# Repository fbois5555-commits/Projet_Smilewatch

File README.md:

# SmileWatch — Montre Connectée Hybride Haute Précision

> **Projet R&D — Conception mécatronique, électronique et horlogère avancée.**  
> Montre hybride alliant l'élégance et la sobriété d'un mouvement analogique à aiguilles, la discrétion d'un affichage numérique micro-OLED, et des capteurs biomédicaux de grade clinique, sans dépendre d'une application propriétaire grâce aux normes universelles Bluetooth SIG.

---

## 🌟 Vision & Philosophie du Projet

La **SmileWatch** est une montre hybride conçue pour répondre à un cahier des charges exigeant :
1. **Élégance horlogère & Discrétion** : Un vrai cadran horloger avec aiguilles physiques animées par un mouvement électromécanique, intégrant subtilement un écran micro-OLED 0.5" pour les notifications et les métriques de santé.
2. **Standard ouvert sans application smartphone dédiée** : Exploitation native des profils Bluetooth SIG standards (CTS, ANCS, HRS, HTS, BAS, DIS) permettant à la montre de fonctionner directement avec iOS et Android (synchronisation de l'heure, notifications directes du smartphone, suivi santé sur Apple Santé / Google Health Connect) sans application tierce requise.
3. **Précision biomédicale** : Capteur optique PPG (fréquence cardiaque & SpO2) et capteur de température cutanée à précision médicale (±0.1 °C) couplé à un insert thermique dédié.
4. **Zéro connecteur / Étanchéité totale** : Châssis métallique monobloc étanche avec recharge inductive sans fil Qi et programmation/test interne via Tag-Connect.

---

## ✨ Fonctionnalités Embarquées Complètes

- **Affichage & Énergie** : 9 écrans × 3 vues (27 vues), mode dynamique `split_6h`, pause mécanique des aiguilles Miyota devant la pilule OLED (`:24..:35`), luminosité adaptative (`VEML6030` → `CH1115`), allumage au regard (`Look-to-Wake`), Mode Nuit / DND, sommeil profond `STOP2`, coupure `+5V_HR` hors séance, charge sans fil Qi (`BQ24040`) et Mode Survie Extrême (`< 10 %` : Miyota seule, podomètre et capteurs coupés).
- **19 Sports, Triathlon & Coach IA** : Musculation, Course, Natation 25m, Vélo, HIIT/Tabata, Rando, Tennis, Boxe, Rameur, Yoga/Cohérence 5s/5s, Corde à sauter, Escalade, Marche rapide, Trail (hydratation 20m), Gainage 30s, Padel, Golf, Ski, Collectif + Triathlon multi-étapes. Détection auto zéro-clic (`LSM6DSOX MLC`), calibration piste `400m/1000m`, calibration GPS/pas BLE, Coach Zones FC (`Z1–Z5`), optimiseur de charge aiguë/chronique et `HRR60`.
- **Santé, Sommeil & Sécurité** : FC, SpO2, HRV (RMSSD), Body Battery, Stress, alerte tachycardie au repos (`>105 BPM` immobile 10 min), réveil doux (`-20 min`), Résumé Réveil + détection pré-maladie (`TMP117` + RHR + HRV), détection & programmation de sieste, détection de chute + compte à rebours SOS `10s` + contact `ICE`.
- **Quotidien, Mémoire & WebBLE Optionnel** : Lampe torche OLED, Chronomètre/Timer, Pomodoro (`25m/5m`), double fuseau horaire, notifications ANCS, GPS Turn-by-Turn, Météo/Agenda, contrôle média/photo BLE HID, alerte sédentarité optionnelle (`50 min`), diagnostic I2C1, FOTA BLE, buffer circulaire Flash `90 %` (`328/365` j) avec rappel et horodatage, plus compagnon WebBLE 0 € ([smilewatch_web.html](smilewatch_web.html)) avec export Strava `.TCX` / `.CSV`.

## 📚 Documentation par Dossier

- [Code/](Code/README.md) — Firmware STM32WB55, drivers I2C1/OLED/Miyota, moteur UI & Flash.
- [Kicad/](Kicad/README.md) — Schémas, PCB 6 couches, antenne RF & empilement.
- [3D/](3D/README.md) — Boîtier Acier 316L SLM/CNC, posage d'assemblage O4 & mécanique.
- [Fabrication_assemblage/](Fabrication_assemblage/README.md) — BOM, plans de montage, étanchéité & procédures.
- [Datasheet/](Datasheet/README.md) — Fiches techniques des composants critiques.

---

## 🛠️ Spécifications Techniques

| Domaine | Caractéristique | Spécification |
| :--- | :--- | :--- |
| **Boîtier / Carrure** | Matériau & Fabrication | **Acier Inox 316L** en **fabrication additive métallique (SLM / DMLS)** avec **reprises d'usinage CNC** des portées critiques (joints, portées d'étanchéité, lunette). |
| **Glace** | Supérieure & Inférieure | Glace supérieure en **Saphir plat** avec joint d'étanchéité Hytrel/Téflon ; fenêtre inférieure en verre minéral optique scellé à la colle UV pour le capteur PPG. |
| **Cadran** | Conception | **Cadran usiné en PCB (FR4 0.4 mm)** faisant office de cadran décoratif (sérigraphie/dorure, index, masquage) avec fenêtre découpée pour l'OLED et passage d'aiguilles. |
| **Mouvement analogique**| Horlogerie | Mouvement quartz **Miyota 2035 modifié (sans couronne)**, dont la bobine du moteur pas-à-pas est directement pilotée par le microcontrôleur via des impulsions électriques étalonnées. |
| **Afficheur numérique** | Écran | **PMOLED 0.5" monochrome (88 × 48 pixels)**, contrôleur **CH1115**, interface I2C, nappe 14 broches repliée sous le cadran avec écran acrylique de protection. |
| **Microcontrôleur (MCU)**| Processeur & Sans-fil | **STMicroelectronics STM32WB55** (Dual-Core : ARM Cortex-M4 @ 64 MHz pour l'applicatif + Cortex-M0+ dédié à la stack RF BLE 5.4), filtre RF intégré **MLPF-WB-02D3**, antenne céramique 2.4 GHz **Johanson 2450AT**. |
| **Capteurs** | Biomédical & Mouvement | • **TMP117** : Température corporelle haute précision (±0.1 °C de grade médical), interfacé via un pont/pad thermique métallique.<br>• **MAX30101** : Capteur optique PPG (Fréquence cardiaque & Oxymétrie de pouls SpO2) avec masque optique Kapton noir anti-diaphonie (120 µm).<br>• **LSM6DSOX** : IMU 6 axes (accéléromètre + gyroscope) avec Machine Learning Core (MLC) pour le podomètre et la reconnaissance de gestes au poignet ultra-basse consommation.<br>• **VEML6030** : Capteur de luminosité ambiante avec guide d'onde lumineux pour l'ajustement automatique de l'OLED. |
| **Interface & Haptique**| I/O & Retours | Contrôleur haptique évolué **TI DRV2605L** + vibreur CMS **HD-EMB1204-SM** ; 2 boutons poussoirs tactiles latéraux étanches **Alps Alpine SKSLLAE010**. |
| **Batterie & Autonomie**| Alimentation | Pile bouton rechargeable Li-Ion **LIR3048 (280 mAh, 3.7 V)** maintenue par contact latéral CMS Harwin (S1921-46R) et calage en mousse Poron. |
| **Recharge** | Sans fil | Récepteur sans fil Qi **TI BQ51003** + bobine de réception Würth Elektronik (**760308101309**) + chargeur linéaire Li-Ion **TI BQ24040**. |
| **Conversion d'énergie**| PMIC & Régulation | Convertisseur élévateur **TPS61023DRLR** (+5.0V pour LEDs capteurs, `R23/R24 = 150k/20k`, inductance **1.0 µH** `DFE18SBN1R0ME0L` `0603`), LDOs +3.3V / +1.8V **TPS7A0233DBVR / TPS7A0218PDBVR** (25 nA), protection batterie **AP9101CAK-ATTRG1** (`C5588142`). |
| **Débogage & Flash** | Connectique | Empreinte **Tag-Connect TC2030-IDC-NL** (SWD 6 broches sans embase physique). |

---

## 📡 Stratégie Bluetooth : Profils Standards & Écosystème

Pour garantir une pérennité totale, une compatibilité multi-OS immédiate et s'affranchir du développement/maintenance d'une application mobile tierce, la SmileWatch implémente directement les **spécifications et profils standardisés Bluetooth SIG et Apple/Android** :

* **CTS (Current Time Service - `0x1805`)** : Synchronisation automatique et transparente de l'heure et du fuseau horaire dès la connexion au smartphone.
* **ANCS (Apple Notification Center Service)** & **Notification Provider Android** : Réception native des alertes (appels entrants, SMS, calendrier, messageries) directement relayées sur l'écran OLED sans passer par une app intermédiaire.
* **HRS (Heart Rate Service - `0x180D`)** : Transmission standardisée de la fréquence cardiaque, reconnue nativement par Apple Santé, Google Health Connect, Strava, Garmin, etc.
* **HTS (Health Thermometer Service - `0x1809`)** : Exportation de la température corporelle clinique mesurée par le TMP117.
* **BAS (Battery Service - `0x180F`)** : Niveau de batterie affiché nativement dans le widget batterie du smartphone.
* **DIS (Device Information Service - `0x180A`)** : Renseignement du nom de modèle, révision hardware, firmware et numéro de série.

---

## 🧩 Architecture Matérielle & Modulaire (Notice V3.8)

L'assemblage physique de la montre repose sur une **architecture recto-verso modulaire à deux sous-ensembles**, assemblés selon une séquence millimétrée :

### 1. Module Supérieur (Face avant)
* **Outillage impératif** : Utilisation d'une **cale 3D d'assemblage (posage O4)** insérée par le bas de la carrure pour encaisser l'effort axial lors du chassage de la glace saphir et préserver le mouvement Miyota.
* **Mouvement horloger** : Positionnement du Miyota 2035 au centre, coiffé par le PCB supérieur (chevauchement de 0.8 mm). Soudure des micro-fils de la bobine du Miyota directement sur les pastilles de 1 mm du PCB supérieur.
* **Carrure flottante & Écran** : Architecture à carrure 316L électriquement flottante (suppression de l'époxy conductrice à l'argent initialement prévue en V3.8, le plan de masse interne 6 couches assurant le contrepoids RF). Soudure directe à plat de la nappe 14 broches (pas 0.62 mm) de l'OLED CH1115, repliement et collage sous le cadran avec fenêtre acrylique.
* **Aiguilles & Chassage Saphir** : Pose des aiguilles des heures et minutes à midi pile, pose du joint Téflon/Hytrel et chassage en force de la glace saphir à la presse d'établi. Retrait de la cale 3D par le bas.

### 2. Module Inférieur (Face arrière & Capteurs)
* **Module thermique** : Insert métallique chassé dans la base polymère, contact thermique avec le capteur TMP117 via pad élastomère.
* **Bobine Qi & Batterie** : Bobine Würth 760308101309 collée dans la base polymère + disque isolant Kapton. Insertion de la batterie LIR3048 (280 mAh) dans le contact latéral CMS, calée par pastille Poron.
* **Optique PPG** : Masque Kapton noir (120 µm) centré sur le MAX30101 (isolation optique émetteur/récepteur), scellement de la glace minérale inférieure à la colle UV.

### 3. Liaison Inter-Modules & Fermeture (Point de non-retour)
* **Interconnexion** : Connecteur THT (Samtec) assurant la liaison électrique rigide entre le PCB supérieur et le PCB capteur inférieur. Soudure par le dessous et arasage des broches à ras. Soudure des micro-fils de la bobine Qi.
* **Fermeture** : Graissage léger du joint torique périphérique (O-ring) de la base polymère et chassage en force du fond dans la carrure (compression axiale finale assurée par les mousses Poron).

---

## 📁 Arborescence du Projet

```text
Projet_Smilewatch/
├── 3D/                          # Fichiers CAO SolidWorks (Pièces .SLDPRT, Assemblages .SLDASM, STEP)
│   ├── carrure.SLDPRT/.STEP     # Boîtier principal (conçu pour impression 3D métal SLM + usinage)
│   ├── Cadran.SLDPRT            # Cadran horloger (conçu sur base PCB FR4 0.4mm)
│   ├── Carte_Capteur_V1/V2.step # Encombrement 3D de la carte capteurs
│   ├── Carte_V1 / Carte_V2.step # Encombrement 3D de la carte mère
│   ├── Miyato_2035.SLDPRT       # Modèle 3D du mouvement horloger
│   ├── Pad_thermique / Pont...  # Pièces de transfert thermique pour le TMP117
│   └── Montre.mp4               # Animation de rendu et cinématique d'assemblage
├── Code/                        # Firmware embarqué sous STM32CubeIDE
│   └── SmileWatch1/             # Projet STM32CubeMX / CubeIDE pour STM32WB55
│       ├── Core/                # Code source C applicatif (main.c, interruptions, init I2C/GPIO)
│       └── Drivers/             # HAL STM32WBxx et CMSIS
├── Commande/                    # Devis, références et paniers de composants (Mouser/Digikey/JLCPCB)
├── Datasheet/                   # Fiches techniques des composants électroniques
│   ├── V1/                      # Datasheets de l'architecture V1 (STM32WB5MMG SiP)
│   └── V2/                      # Datasheets de l'architecture V2 (STM32WB55, filtres, antenne)
├── Fabrication_assemblage/      # Guides et documents de fabrication
│   └── Notice_montage_montre.pdf# Manuel d'intégration mécanique modulaire recto-verso (V3.8)
├── Kicad/                       # Projets de CAO électronique KiCad
│   ├── Carte_V1/                # Première itération matérielle
│   ├── Carte_V2/                # Schémas hiérarchiques et PCB v2 (MCU, Alim Qi, Capteurs, Écran, Moteur)
│   │   ├── Carte_Capteur_V2/    # Sous-carte capteurs (TMP117, MAX30101, boost TPS61023, TCA9517D) & production/
│   │   └── production/          # Fichiers de fabrication PCB (Gerbers, Drill, CPL, BOM JLCPCB)
│   └── Composant/               # Empreintes et symboles personnalisés
├── Media/                       # Rendu 3D, photos, vues éclatées et transparentes
├── README.md                    # Présentation et documentation centrale du projet
└── REFLEXIONS.md                # Carnet d\'idées, backlog et points d\'attention techniques
```

---

## 🎯 Statut Actuel & Feuille de Route

- [x] **Architecture système & Sélection des composants** : Définition complète (STM32WB55 WLCSP-100, LIR3048 280 mAh, Qi BQ51003, capteurs cliniques).
- [x] **CAO Mécanique 3D (SolidWorks 2026) & PCB Cadran FR4** : Modélisation carrure, base, verres, posage O4 et conception du cadran horloger FR4 0.4 mm (dorure ENIG sur masque noir mat).
- [x] **Notice de montage modulaire** : Rédaction du manuel d'intégration mécanique (V3.8, mise à jour V3.9 prévue).
- [x] **Audit d'Ingénierie Global 360° (08 Novembre 2026)** : Inspection intégrale sans approximation des 3 PCB KiCad 10, des datasheets constructeurs et des 50 interférences SolidWorks de `Montre.SLDASM` (détails et correctifs consignés dans `REFLEXIONS.md` §13 et `suivi_projet.html`).
- [x] **Passe Corrective Électronique, Datasheets & BOM V2.1 (11 Novembre 2026)** :
  - **`Carte_V2`** : Polarité batterie `LIR3048` corrigée (`BT1` = `C22` latéral `+3V8`, `TP8` `6×6 mm` sur `GNDPWR`, `TP2` supprimé — *point d'attention : contact central plat excentré à $r=11.05\text{ mm}$ sans ressort*) ; switch OLED `Q1`/`Q2` câblé (`Q2.2` à `GND`, `Q1.2`+`R15` sur `+3V8`, `R13 = 560 kΩ`) ; RF corrigée (`R21`/`R24 = DNP` + `in_pos_files no`, Keepout 6 couches `ANT1`, quartz `Y1 = ABM13W 8 pF` + `12 pF C0G`) ; pont ADC `VBAT` (`2×1 MΩ + 100 nF` sur `PC4`), LDOs `TPS7A0233/18`, `R5 = 1.5 kΩ`, `R7 = DNP`, `C46 = 100 nF`, `R16 = 330 Ω`, `U4 = AP9101CAK-ATTRG1` (`C5588142`, Auto-Wake-Up), `C0G2_50V1 = 220 nF` (`C21120`), `R27 = 10 kΩ` (`C25744`, remplace `TH2`), `TH1 = 10k NTC` (`C91636`), assainissement complet des `JLCPCB Part#` passifs. **ERC = 0 erreur (62 warnings), DRC (règles projet) + parité = 0 violation, 0 non connecté** *(20 alertes `--severity-all` préexistantes connues sur `S1/S2` bord `0.17–0.19 mm` et freins thermiques `IC2`)*.
  - **`Carte_Capteur_V1` & `Cadran`** : Boost `+5.0V` migré vers **`TPS61023DRLR`** (`IC3`, `C919459`, stk `6 681`) + **`L1 = 1.0 µH` `0603` (`DFE18SBN1R0ME0L`, `C882989`, stk `2 188`)** + **`R23 = 150 kΩ` (`C25755`) / `R24 = 20 kΩ` (`C25765`)** + `C18/C19 = 10 µF` (`C96446`) ; **`U3 = TCA9517DR`** (`C182421`, **stk `5 738` en stock JLC**) inversé et rerouté Side A (`+1V8` MAX30101) / Side B (`+3V3` MCU) ; îlot thermique `B.Cu` + 2 vias + keepout `U2_Thermal_Iso` sous `TMP117` (`U2`). **ERC = 0 erreur (`11` warnings), DRC + parité = 0 violation** (`Cadran` inchangé avec marge OLED conservée : ERC `0` / DRC `0` erreur, `55` warnings sérigraphie bord).
  - **Datasheets & Livrables usine mis à jour** : `Datasheet/V2/` actualisé (`tps61023.pdf`, `tps7a02.pdf` EN `SBVS277C`, `ABM13W`, `NCP15XH103F0SRC`, `DFE18SBN1R0ME0L`, `Samtec_TW_Series`, `CL10A106MA8NRNC.pdf`, `GRM1555C1H222GA01D.pdf` ; retrait `MAX17220`, `AP2127`, `Hirose`, `74438323100`), packages **`production/`** (Gerbers `.zip`, Drill, IPC-356, `bom.csv`, `positions.csv`) régénérés pour les 3 cartes, BOM schémas `Carte_V2.csv` / `Carte_Capteur_V1.csv` à jour, et modèles **`3D/Carte_V2.3f.step`** / **`3D/Carte_Capteur_V2f.step`** ré-exportés.
- [x] **Finalisation Routage, Empreintes JLC & Modèles 3D `Carte_V2` (14 Novembre 2026)** :
  - **Empreintes & Modèles 3D** : Bibliothèque `Smilewatch_V2_JLC.pretty` et `Carte_V2.kicad_pcb` mises à jour avec chemins `.step` corrigés (`${KIPRJMOD}/../Composant/...`) pour `ANT1`, `FL1`, `Y1`, `Q3`, `IC2`, et création de `LD-SM-430.step` (`4,0 × 11,0 × 3,6 mm`) pour le moteur `M1`.
  - **Antenne `ANT1` & RF `50 Ω`** : Zone keep-out `4,0 × 6,0 mm` 6 couches intégrée à `ANT1` (`Pin 4 = FEED`, `Pin 1–3 = GND`), placée à `2,81 mm` du bord (`R = 19,45 mm`, un seul coin déborde de `0,35 mm`, `BT1` hors zone active) ; ligne coplanaire `GCPW` ajustée à **`0,135 mm`** / jeu **`0,10 mm`** pour le stackup **`JLC06081H-2116`** (`0,8 mm`, 6 couches, `0,1349 mm` sur l'`Impedance calculator` JLCPCB, ~100 € moins cher que `2313`), sur `U2.K4 → FL1 → Pi-network R21/R22/R24 → ANT1.4` avec plan `In1.Cu` continu et vias de couture `GND`.
  - **Prochaine étape immédiate (`19 Nov 2026` — Jalon critique `< 16 Déc`)** : **Carrures SLM 316L (`x4`, `3D/carrure_fabrication.SLDPRT`) payées et en attente de livraison** ; **taraud + 2× Miyota 2035 reçus (`18 Nov`)** ; **inversion des clips faite** et **firmware en très bonne voie**. Côté électronique : **`positions.csv` corrigé (`ANT1` `90°`, `IC1` `0°`, `IC4`/`IC6` `180°`, `IC8` `270°`)** ; à la réception de `U2` (**26 Nov**), ré-uploader `positions.csv`, vérifier `U4` (`bottom`) en 3D et lancer immédiatement le PCBA (`JLC06081H-2116`, `Depanel = Yes`, livraison express pour réception **avant le 16 décembre** — sinon reprise repoussée au **8 janvier** pour une fin le **22 janvier**).
- [ ] **Verrouillage avant commande Usine (Points Méca, Datasheets & Sourcing en attente)** :
  - **Mécanique CAO (`Montre.SLDASM`)** : Portée saphir (`+1.35 mm`), gorge O-ring ISO 3601 (25 %), `Batterie.SLDPRT` (`4.90 mm`) et `Canal_lum.SLDPRT` travaillés (`09/11`, proto PLA lancé) ; **inversion des clips `Base`/`carrure` effectuée** (`19 Nov`) ; `3D/carrure.SLDPRT` (`51,04 × 44,21 × 9,65 mm`) conservée aux cotes finales et **clone fabrication `3D/carrure_fabrication.SLDPRT` commandé en `x4` SLM 316L (`19 Nov`, payé — en attente livraison)** ; reprise prévue à réception : alésage tour + perçage + **chanfrein 45°** + taraudage poussoirs. **Contrôles restants sur `Base.SLDPRT` / assemblage** : statuer sur les composants `F.Cu` sous la dalle OLED (`Q1`, `Q2`, `7×0603` `[P0-MECA-7]`), confirmer poche sous `J1` + lamage Qi dans `Base.SLDPRT` `[P0-MECA-6]`, intégrer poussoirs étanches `Bouton.SLDASM` `[P1-MECA-9]` et vérifier dégagement radial `TPS61023`/`L1 0603` `[P1-MECA-10]`.
  - **Points d'attention Datasheets JLC (`V2.1`)** : **`U4` (`AP9101CAK-ATTRG1` `C5588142`, stk `162` ✅)** = variante `CAK` **Auto-Wake-Up** (`VCU=4.400 V` protégée en aval par `BQ24040` à `4.20 V`, `VDL=2.800 V` adaptée à la `LIR3048`, `0 V` autorisée) ; **`C0G2_50V1` (`C21120` `CL10B224KA8NNNC`)** = `220 nF 25 V X7R` (au lieu de `C0G 50 V`) sur résonance série Qi `10 µH` (`760308101309`) ; **`TPS61023` (`IC3`)** alimenté par `IC6` (`TPS7A0233` `200 mA` max ➔ pulses `MAX30101` `≤ 50 mA`), `+5.06 V` typ (`C19/C26 = 2×10 µF 25V X5R`).
  - **Sourcing JLCPCB SMT (`19 Nov 2026`)** : Tous les composants JLC de `Carte_Capteur_V1` sont en stock (`J1` main). Sur **`Carte_V2`** (`bom.csv` réaligné sur KiCad, `46` lignes / `99` composants) : **`IC1`, `IC8`, `FL1`, `TH1` sécurisés dans `My Parts`** ; `ANT1` (`646`), `Y1` (`380`), `M1` (`2 382`), `Q3` (`170 444`) en stock public ; **seul `U2` (`C1850399`) reste en attente de livraison (reporté au 26 Nov)** (activer **Epoxy Filled & Capped** + `JLC06081H-2116`). Hors-PCBA à souder/monter manuellement : `C39`, `J2`, `BT1`/`TP8`, `TP1`/`TP3`, `TP6`/`TP7`.
  - **Firmware `[P2-FW-16]`** : **En très bonne voie** (`19 Nov`).
- [ ] **Fabrication des prototypes matériels** :
  - Commande de la carrure en fabrication additive métallique (SLM/DMLS Inox 316L) + reprise CNC et fabrication de la Base.
  - Fabrication et assemblage PCB (PCBA JLCPCB pour carte mère 6 couches, carte capteurs et cadran).
- [ ] **Développement Firmware (`STM32WB55VGYx` WLCSP-100)** :
  - Création du nouveau projet STM32CubeIDE sur cible `STM32WB55VGYx` (remplaçant le squelette V1 `STM32WB5MMGHx`) avec `HSE 32 MHz`, `LSE` et pile BLE double-cœur (`STM32_WPAN` + OTA).
  - Implémentation des profils BLE standards (CTS, ANCS, HRS, HTS, BAS, DIS).
  - Pilote pas-à-pas bipolaire amorti (impulsion calibrée + freinage électrodynamique `LOW-LOW`) pour le mouvement Miyota 2035.
  - Driver I2C DMA pour l'affichage CH1115 (OLED 88×48) et les capteurs, et gestion veille ultra-basse consommation (`STOP 2` + réveil MLC `LSM6DSOX`).

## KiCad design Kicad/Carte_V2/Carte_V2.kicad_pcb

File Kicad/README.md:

# Kicad — Conception Électronique & PCB

Ce dossier regroupe les schémas électriques, le routage PCB et les bibliothèques KiCad de la SmileWatch.

## Points Clés Matériels

- **Architecture 6 couches** : séparation stricte des plans de masse analogique/RF/puissance et intégration dans un encombrement circulaire horloger.
- **Cœur RF & MCU** : `STM32WB55VGYx` (WLCSP-100), filtre RF intégré `MLPF-WB-02D3`, antenne céramique 2.4 GHz `Johanson 2450AT` avec carrure acier 316L flottante.
- **Capteurs I2C1** : `LSM6DSOX` (`0x6A`), `MAX30101` (`0x57`), `TMP117` (`0x48`), `VEML6030` (`0x10`), `DRV2605L` (`0x5A`), écran PMOLED `CH1115` (`0x3C`).
- **Alimentation & Recharge Qi** : Récepteur sans fil `BQ51003` + chargeur Li-Ion `BQ24040` pour pile `LIR3048`, boost `+5V` `TPS61023` commandé par `HR_5V_EN`, LDOs `TPS7A0233` / `TPS7A0218` (`25 nA`).
- **Programmation** : Empreinte `Tag-Connect TC2030-IDC-NL` (SWD 6 broches sans connecteur).

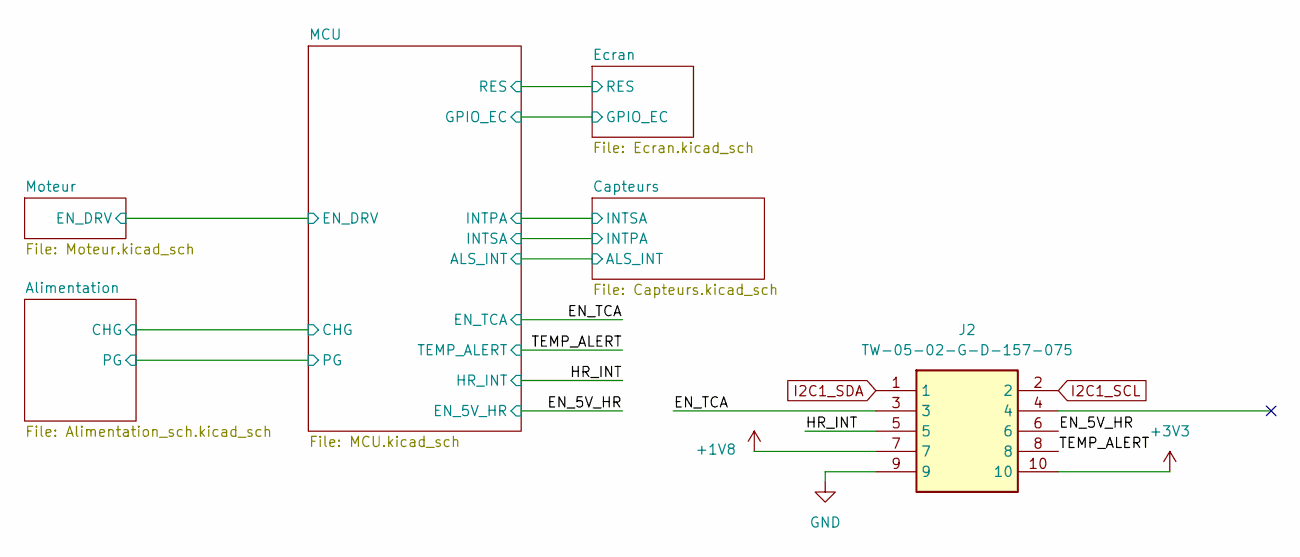
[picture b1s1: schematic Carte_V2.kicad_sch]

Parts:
J2: TW-05-02-G-D-157-075; HDRV10W51P200_2X5_1000X400X769P; Mouser Part Number 200-TW0502GD157075

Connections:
+1V8: J2.7; also elsewhere on the board
/EN_5V_HR: J2.6; also elsewhere on the board
/EN_TCA: J2.3; also elsewhere on the board
/HR_INT: J2.5; also elsewhere on the board
/TEMP_ALERT: J2.8; also elsewhere on the board
I2C1_SCL: J2.2; also elsewhere on the board
I2C1_SDA: J2.1; also elsewhere on the board

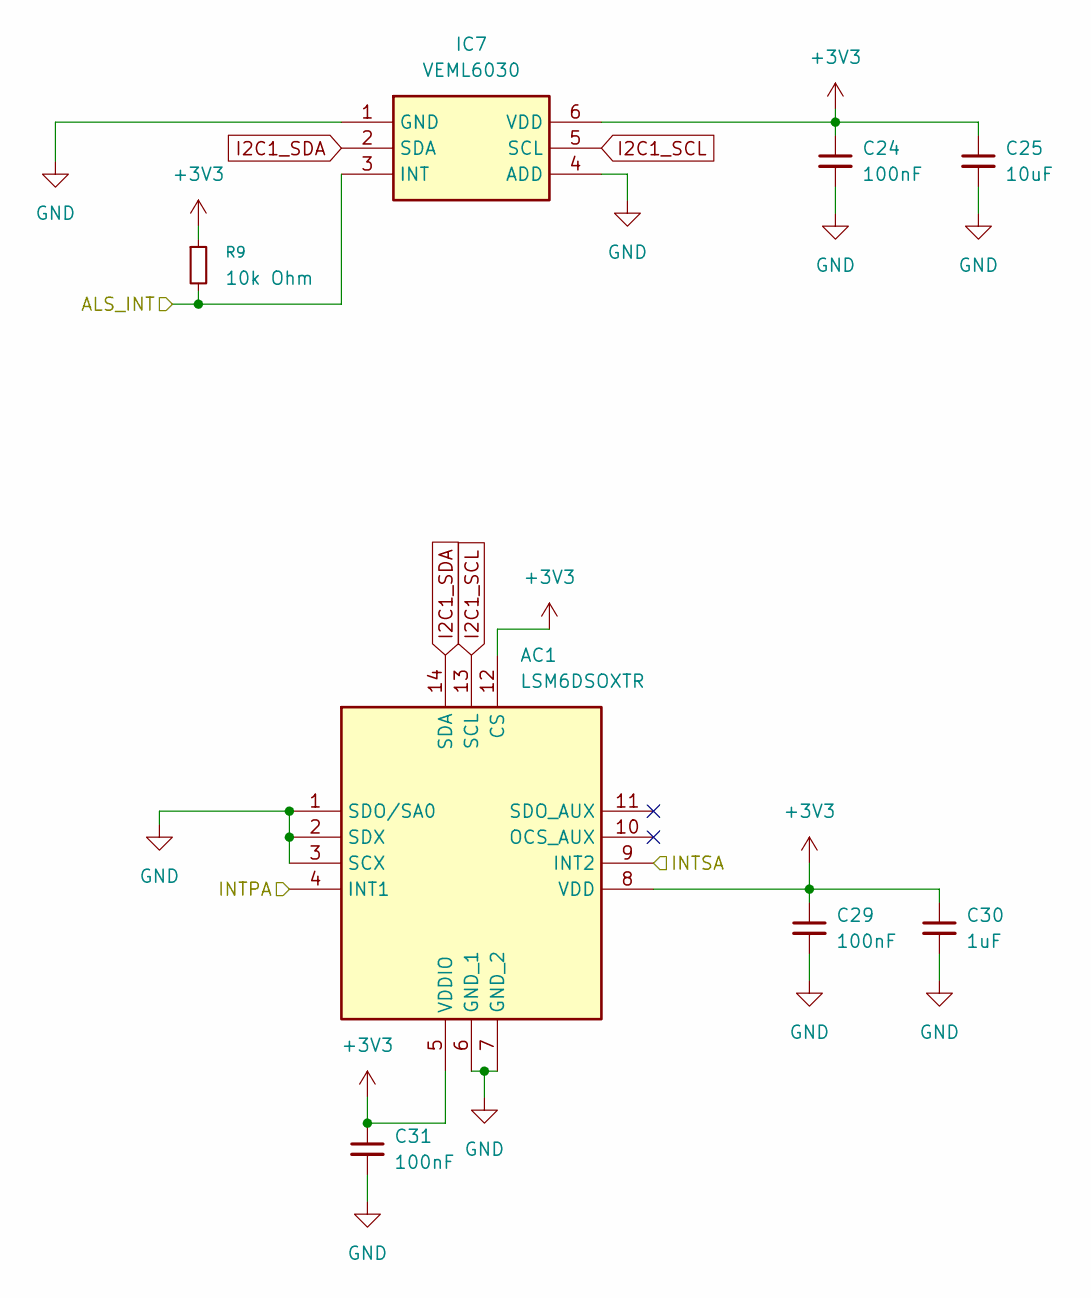
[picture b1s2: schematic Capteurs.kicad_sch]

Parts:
AC1: LSM6DSOXTR; LGA-14_1; Mouser Part Number 511-LSM6DSOXTR
C24, C29, C31: 100nF; C_0402_1005Metric; JLCPCB Part# C1525
C25: 10uF; C_0603_1608Metric; JLCPCB Part# C96446
C30: 1uF; C_0603_1608Metric; JLCPCB Part# C15849
IC7: VEML6030; Mouser Part Number 78-VEML6030
R9: 10k Ohm; R_0402_1005Metric; JLCPCB Part# C25744

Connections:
/Capteurs/ALS_INT: IC7.3 (INT), R9.2; also elsewhere on the board
/Capteurs/INTPA: AC1.4 (INT1); also elsewhere on the board
/Capteurs/INTSA: AC1.9 (INT2); also elsewhere on the board
I2C1_SCL: AC1.13 (SCL), IC7.5 (SCL); also elsewhere on the board
I2C1_SDA: AC1.14 (SDA), IC7.2 (SDA); also elsewhere on the board

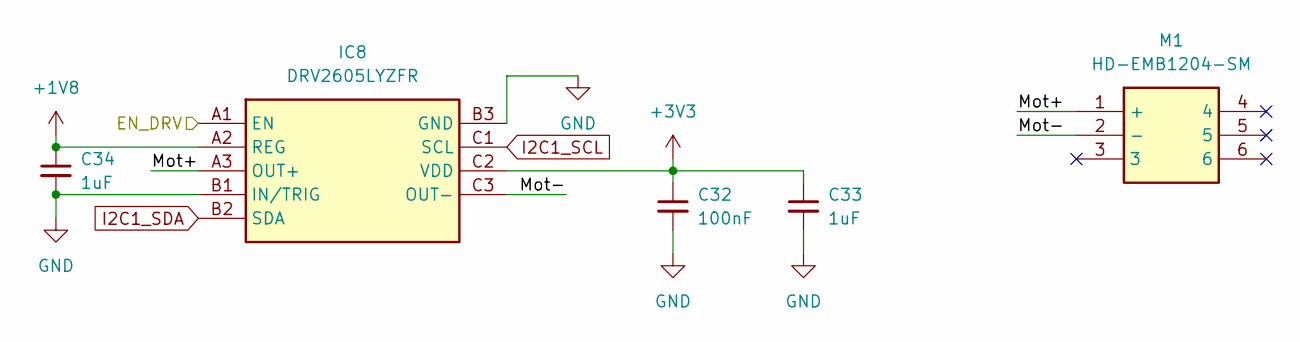
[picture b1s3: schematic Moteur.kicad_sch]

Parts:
C32: 100nF; C_0402_1005Metric; JLCPCB Part# C1525
C33, C34: 1uF; C_0603_1608Metric; JLCPCB Part# C15849
IC8: DRV2605LYZFR; BGA9C50P3X3_144X144X62; Mouser Part Number 595-DRV2605LYZFR
M1: HD-EMB1204-SM; HDEMB1204SM; Mouser Part Number 665-HD-EMB1204-SM

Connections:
/MCU/EN_DRV: IC8.A1 (EN); also elsewhere on the board
/Moteur/Mot+: IC8.A3 (OUT+), M1.1 (+)
/Moteur/Mot-: IC8.C3 (OUT-), M1.2 (-)
I2C1_SCL: IC8.C1 (SCL); also elsewhere on the board
I2C1_SDA: IC8.B2 (SDA); also elsewhere on the board
unnamed: C34.1, IC8.A2 (REG)

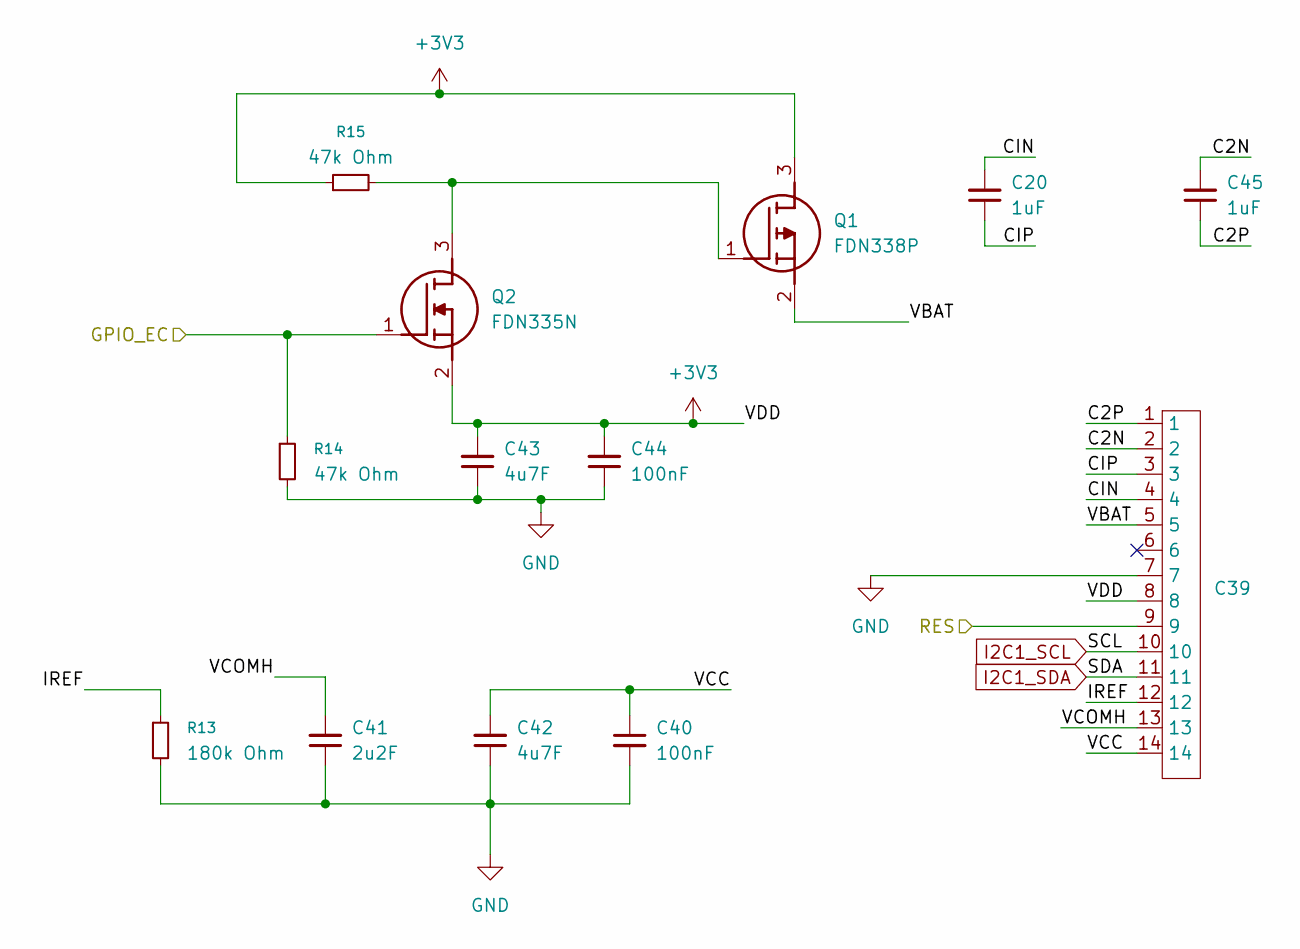
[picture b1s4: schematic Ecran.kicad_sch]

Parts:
C20, C45: 1uF; C_0603_1608Metric; JLCPCB Part# C15849
C39: ConnectorMicromatch-14
C40, C44: 100nF; C_0402_1005Metric; JLCPCB Part# C1525
C41: 2u2F; C_0603_1608Metric; JLCPCB Part# C23630
C42, C43: 4u7F; C_0603_1608Metric; JLCPCB Part# C19666
Q1: FDN338P; TSOT-23; Mouser Part Number 512-FDN338P
Q2: FDN335N; TSOT-23; Mouser Part Number 512-FDN335N
R13: 180k Ohm; R_0402_1005Metric; JLCPCB Part# C25541
R14, R15: 47k Ohm; R_0402_1005Metric; JLCPCB Part# C176117

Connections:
/Ecran/C2N: C39.2, C45.2
/Ecran/C2P: C39.1, C45.1
/Ecran/CIN: C20.2, C39.4
/Ecran/CIP: C20.1, C39.3
/Ecran/GPIO_EC: Q2.1 (G), R14.1; also elsewhere on the board
/Ecran/IREF: C39.12, R13.1
/Ecran/RES: C39.9; also elsewhere on the board
/Ecran/VCC: C39.14, C40.1, C42.2
/Ecran/VCOMH: C39.13, C41.2
I2C1_SCL: C39.10; also elsewhere on the board
I2C1_SDA: C39.11; also elsewhere on the board
unnamed: Q1.1 (G), Q2.3 (D), R15.2

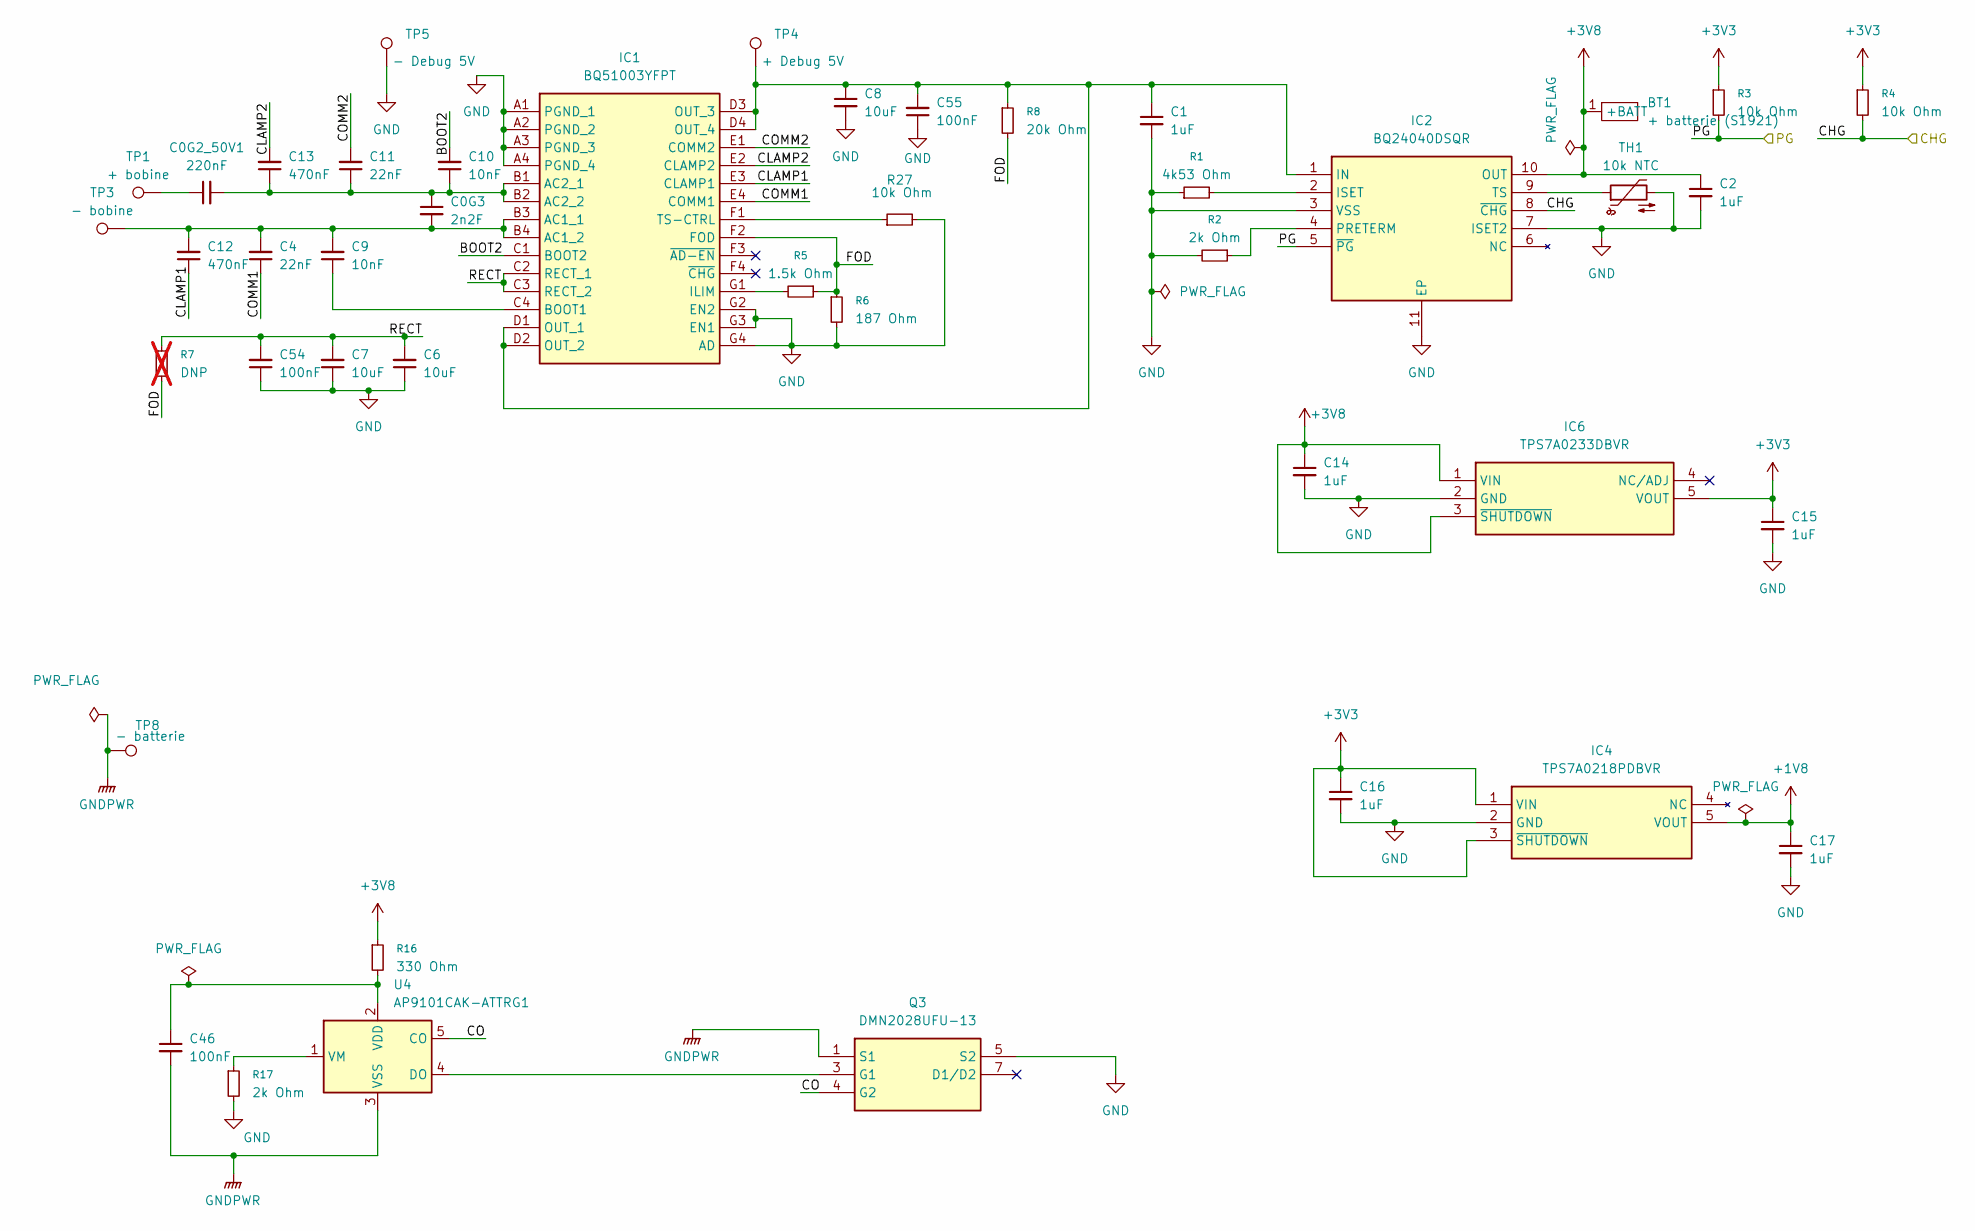
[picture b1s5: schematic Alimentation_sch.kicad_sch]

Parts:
BT1: + batterie (S1921); S1921
C0G2_50V1: 220nF; C_0603_1608Metric; JLCPCB Part# C21120
C0G3: 2n2F; C_0402_1005Metric; JLCPCB Part# C2987940
C1, C2, C14, C15, C16, C17: 1uF; C_0603_1608Metric; JLCPCB Part# C15849
C4, C11: 22nF; C_0402_1005Metric; JLCPCB Part# C1532
C6, C7, C8: 10uF; C_0603_1608Metric; JLCPCB Part# C96446
C9, C10: 10nF; C_0402_1005Metric; JLCPCB Part# C15195
C12, C13: 470nF; C_0402_1005Metric; JLCPCB Part# C92361
C46: 100nF; C_0603_1608Metric; JLCPCB Part# C14663
C54, C55: 100nF; C_0402_1005Metric; JLCPCB Part# C1525
IC1: BQ51003YFPT; BGA28C40P4X7_188X301X50; Mouser Part Number 595-BQ51003YFPT
IC2: BQ24040DSQR; WSON-10-1EP_2.5x2.5mm_P0.5mm_EP1.2x2mm_ThermalVias; Mouser Part Number 595-BQ24040DSQR
IC4: TPS7A0218PDBVR; SOT95P282X145-5N; Manufacturer_Part_Number TPS7A0218PDBVR; JLCPCB Part# C3748843
IC6: TPS7A0233DBVR; SOT95P282X145-5N; Manufacturer_Part_Number TPS7A0233DBVR; JLCPCB Part# C5142805
Q3: DMN2028UFU-13; DMN2028UFU7; Mouser Part Number 621-DMN2028UFU-13
R1: 4k53 Ohm; R_0402_1005Metric; JLCPCB Part# C3015988
R2, R17: 2k Ohm; R_0402_1005Metric; JLCPCB Part# C4109
R3, R4, R27: 10k Ohm; R_0402_1005Metric; JLCPCB Part# C25744
R5: 1.5k Ohm; R_0402_1005Metric; JLCPCB Part# C25867
R6: 187 Ohm; R_0402_1005Metric; JLCPCB Part# C39887
R7: DNP; R_0402_1005Metric; not fitted
R8: 20k Ohm; R_0402_1005Metric; JLCPCB Part# C25765
R16: 330 Ohm; R_0402_1005Metric; JLCPCB Part# C25104
TH1: 10k NTC; R_0402_1005Metric; JLCPCB Part# C91636
TP1: + bobine; TestPoint_Pad_D1.0mm
TP3: - bobine; TestPoint_Pad_D1.0mm
TP4: + Debug 5V; TestPoint_Pad_D1.0mm
TP5: - Debug 5V; TestPoint_Pad_1.0x1.0mm
TP8: - batterie; TestPoint_Pad_D4.0mm
U4: AP9101CAK-ATTRG1; SOT-23-5; JLCPCB Part# C5588142

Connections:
+1V8: C17.1, IC4.5 (VOUT); also elsewhere on the board
/Alimentation/BOOT2: C10.2, IC1.C1 (BOOT2)
/Alimentation/CHG: IC2.8 (~CHG), R4.2; also elsewhere on the board
/Alimentation/CLAMP1: C12.1, IC1.E3 (CLAMP1)
/Alimentation/CLAMP2: C13.2, IC1.E2 (CLAMP2)
/Alimentation/CO: Q3.4 (G2), U4.5 (CO)
/Alimentation/COMM1: C4.1, IC1.E4 (COMM1)
/Alimentation/COMM2: C11.2, IC1.E1 (COMM2)
/Alimentation/FOD: IC1.F2 (FOD), R5.1, R6.1, R7.2, R8.2
/Alimentation/PG: IC2.5 (~PG), R3.2; also elsewhere on the board
/Alimentation/RECT: C6.2, C7.2, C54.2, IC1.C2 (RECT_1), IC1.C3 (RECT_2), R7.1
GNDPWR: C46.2, Q3.1 (S1), TP8.1 (1_1), U4.3 (VSS)
unnamed: C0G2_50V1.1, TP1.1 (1_1)
unnamed: C0G3.2, C4.2, C9.2, C12.2, IC1.B3 (AC1_1), IC1.B4 (AC1_2), TP3.1 (1_1)
unnamed: C0G2_50V1.2, C0G3.1, C10.1, C11.1, C13.1, IC1.B1 (AC2_1), IC1.B2 (AC2_2)
unnamed: C9.1, IC1.C4 (BOOT1)
unnamed: IC1.G1 (ILIM), R5.2
unnamed: C1.1, C8.1, C55.2, IC1.D1 (OUT_1), IC1.D2 (OUT_2), IC1.D3 (OUT_3), IC1.D4 (OUT_4), IC2.1 (IN), R8.1, TP4.1 (1_1)
unnamed: IC1.F1 (TS-CTRL), R27.1
unnamed: IC2.2 (ISET), R1.2
unnamed: IC2.4 (PRETERM), R2.1
unnamed: IC2.9 (TS), TH1.1
unnamed: C46.1, R16.2, U4.2 (VDD)
unnamed: R17.1, U4.1 (VM)

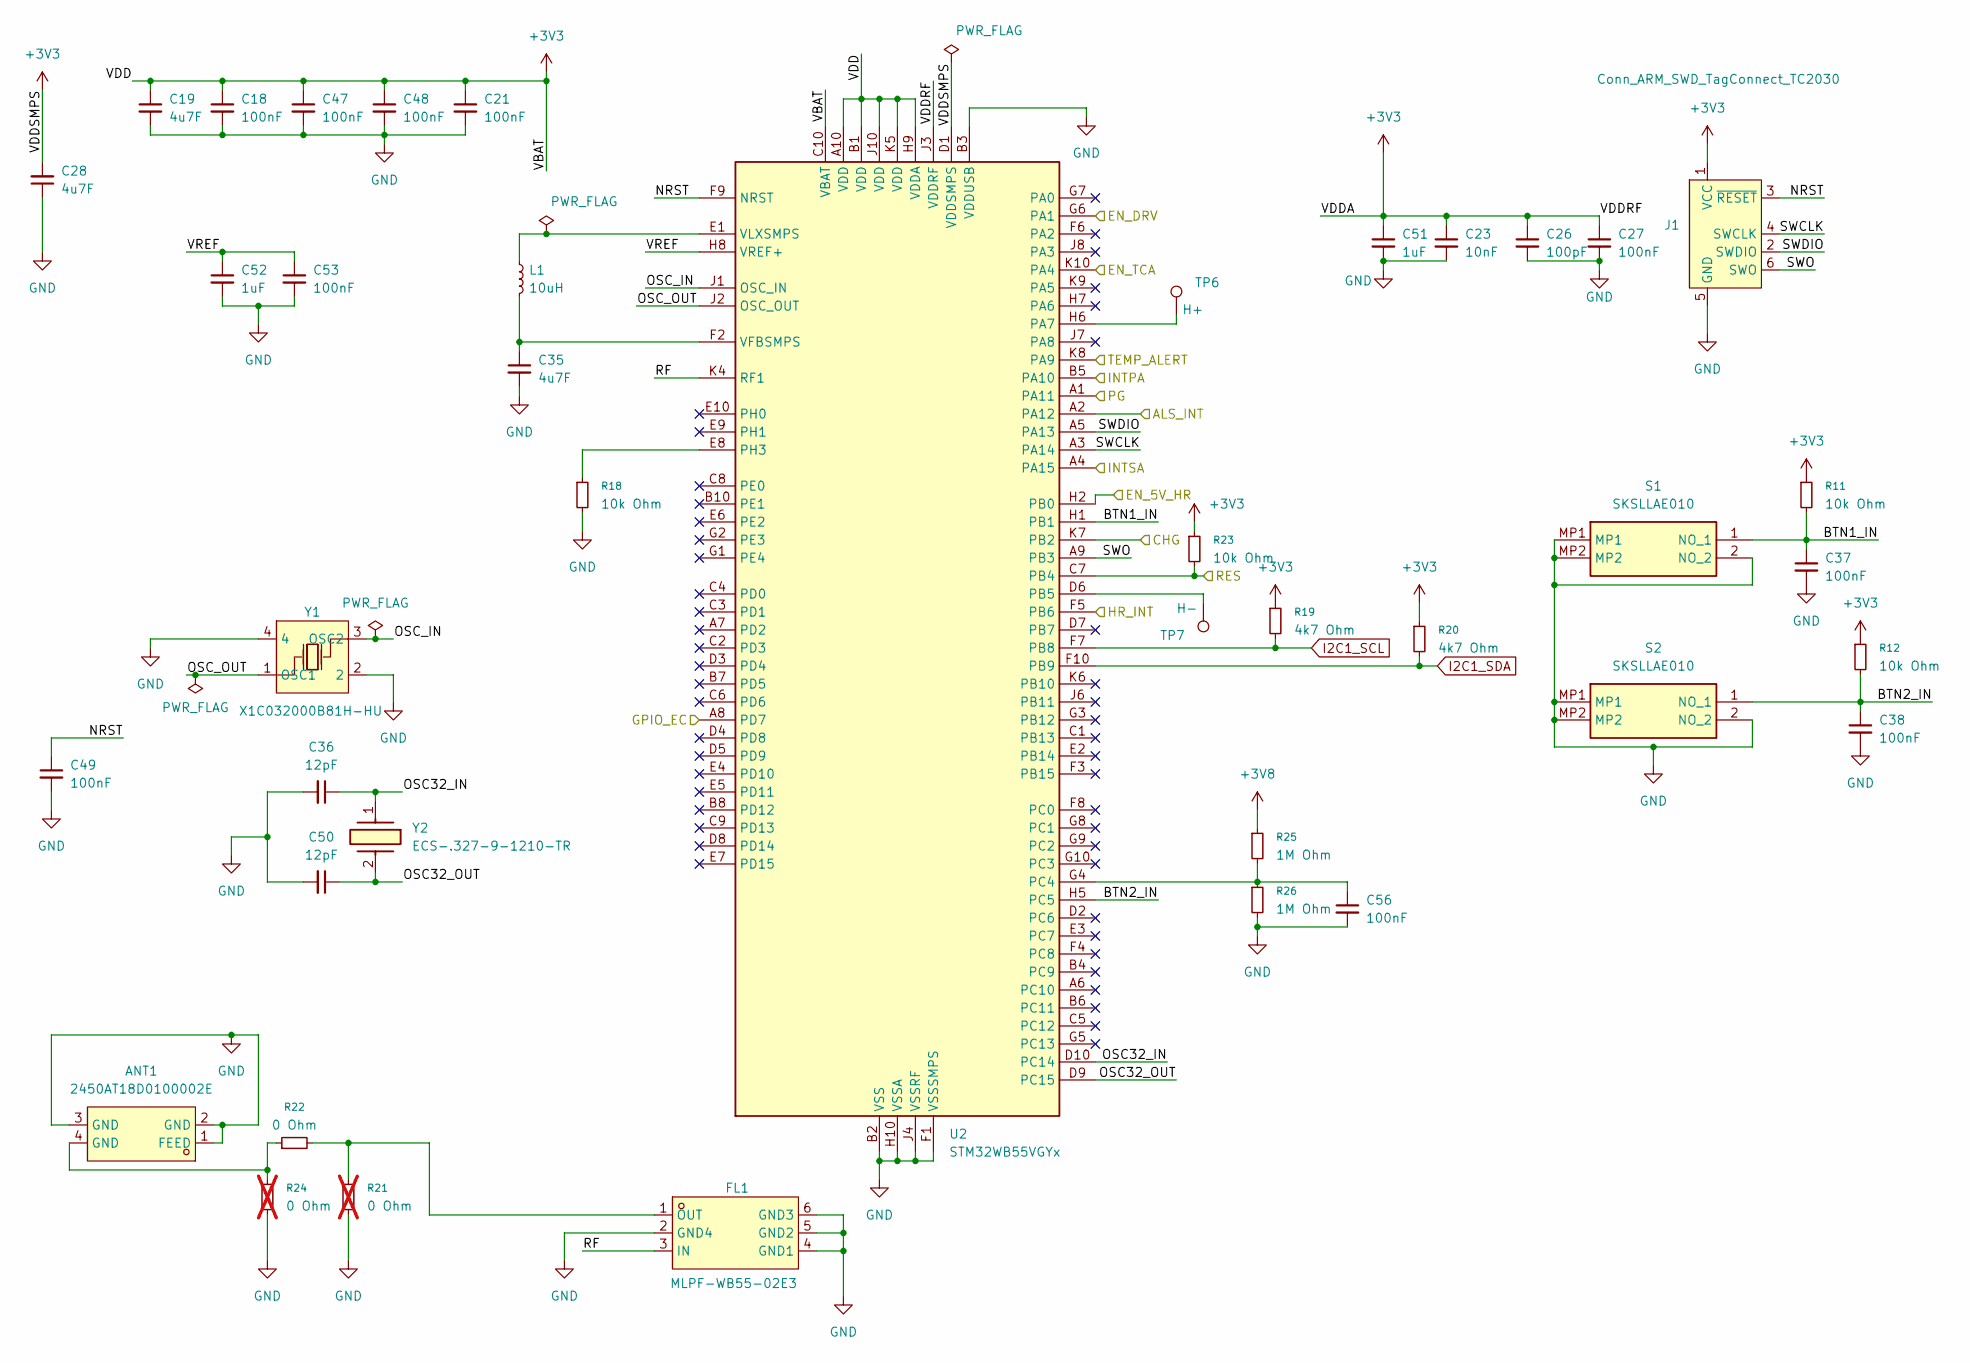
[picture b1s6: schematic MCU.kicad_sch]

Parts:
ANT1: 2450AT18D0100002E; ANT-SMD_4P-L3.2-W1.6; LCSC C17410360
C18, C21, C27, C37, C38, C48, C49, C53, C56: 100nF; C_0402_1005Metric; JLCPCB Part# C1525
C19, C28, C35: 4u7F; C_0603_1608Metric; JLCPCB Part# C19666
C23: 10nF; C_0402_1005Metric; JLCPCB Part# C15195
C26: 100pF; C_0402_1005Metric; JLCPCB Part# C1546
C36, C50: 12pF; C_0402_1005Metric; JLCPCB Part# C1547
C47: 100nF; C_0201_0603Metric; JLCPCB Part# C284966
C51, C52: 1uF; C_0603_1608Metric; JLCPCB Part# C15849
FL1: MLPF-WB55-02E3; FILTER-SMD_6P-L1.6-W1.0-P0.50-BL; LCSC C1855732
J1: Conn_ARM_SWD_TagConnect_TC2030; Tag-Connect_TC2030-IDC-NL_2x03_P1.27mm_Vertical
L1: 10uH; L_1008_2520Metric; JLCPCB Part# C37428
R11, R12, R18, R23: 10k Ohm; R_0402_1005Metric; JLCPCB Part# C25744
R19, R20: 4k7 Ohm; R_0402_1005Metric; JLCPCB Part# C25900
R21, R24: 0 Ohm; R_0402_1005Metric; JLCPCB Part# C60485; not fitted
R22: 0 Ohm; R_0402_1005Metric; JLCPCB Part# C60485
R25, R26: 1M Ohm; R_0402_1005Metric; JLCPCB Part# C26083
S1, S2: SKSLLAE010; Mouser Part Number 688-SKSLLAE010
TP6: H+; TestPoint_Pad_D1.0mm
TP7: H-; TestPoint_Pad_D1.0mm
U2: STM32WB55VGYx; ST_WLCSP-100_4.4x4.38mm_Layout10x10_P0.4mm_Offcenter; JLCPCB Part# C1850399
Y1: X1C032000B81H-HU; OSC-SMD_4P-L1.6-W1.2-BL; LCSC C254218
Y2: ECS-.327-9-1210-TR; ECS32791210TR; Mouser Part Number 520-.327-7-1210T

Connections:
/Alimentation/CHG: U2.K7 (PB2); also elsewhere on the board
/Alimentation/PG: U2.A1 (PA11); also elsewhere on the board
/Capteurs/ALS_INT: U2.A2 (PA12); also elsewhere on the board
/Capteurs/INTPA: U2.A4 (PA15); also elsewhere on the board
/Capteurs/INTSA: U2.B5 (PA10); also elsewhere on the board
/EN_5V_HR: U2.H2 (PB0); also elsewhere on the board
/EN_TCA: U2.K10 (PA4); also elsewhere on the board
/Ecran/GPIO_EC: U2.A8 (PD7); also elsewhere on the board
/Ecran/RES: R23.2, U2.C7 (PB4); also elsewhere on the board
/HR_INT: U2.F5 (PB6); also elsewhere on the board
/MCU/BTN1_IN: C37.1, R11.2, S1.1 (NO_1), U2.H1 (PB1)
/MCU/BTN2_IN: C38.1, R12.2, S2.1 (NO_1), U2.H5 (PC5)
/MCU/EN_DRV: U2.G6 (PA1); also elsewhere on the board
/MCU/NRST: C49.1, J1.3 (~RESET), U2.F9 (NRST)
/MCU/OSC32_IN: C36.1, U2.D10 (PC14), Y2.1
/MCU/OSC32_OUT: C50.1, U2.D9 (PC15), Y2.2
/MCU/OSC_IN: U2.J1 (OSC_IN), Y1.3 (OSC2)
/MCU/OSC_OUT: U2.J2 (OSC_OUT), Y1.1 (OSC1)
/MCU/RF: FL1.3 (IN), U2.K4 (RF1)
/MCU/SWCLK: J1.4 (SWCLK), U2.A3 (PA14)
/MCU/SWDIO: J1.2 (SWDIO), U2.A5 (PA13)
/MCU/SWO: J1.6 (SWO), U2.A9 (PB3)
/MCU/VREF: C52.1, C53.1, U2.H8 (VREF+)
/TEMP_ALERT: U2.K8 (PA9); also elsewhere on the board
I2C1_SCL: R19.2, U2.F7 (PB8); also elsewhere on the board
I2C1_SDA: R20.2, U2.F10 (PB9); also elsewhere on the board
unnamed: ANT1.4 (GND), R22.1, R24.2
unnamed: FL1.1 (OUT), R21.2, R22.2
unnamed: TP6.1 (1_1), U2.H6 (PA7)
unnamed: TP7.1 (1_1), U2.D6 (PB5)
unnamed: C56.1, R25.2, R26.1, U2.G4 (PC4)
unnamed: R18.1, U2.E8 (PH3)
unnamed: C35.1, L1.2, U2.F2 (VFBSMPS)
unnamed: L1.1, U2.E1 (VLXSMPS)

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
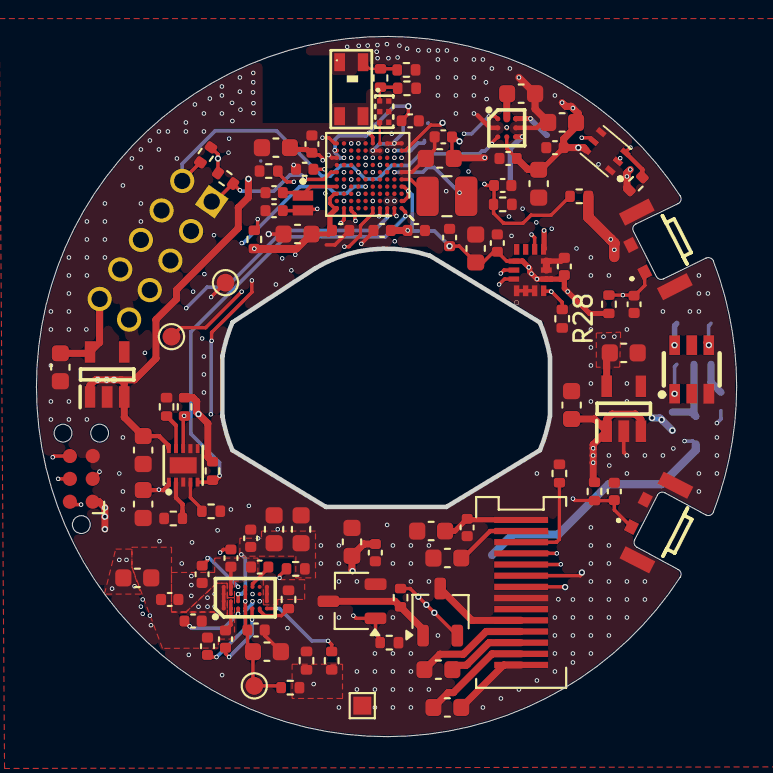
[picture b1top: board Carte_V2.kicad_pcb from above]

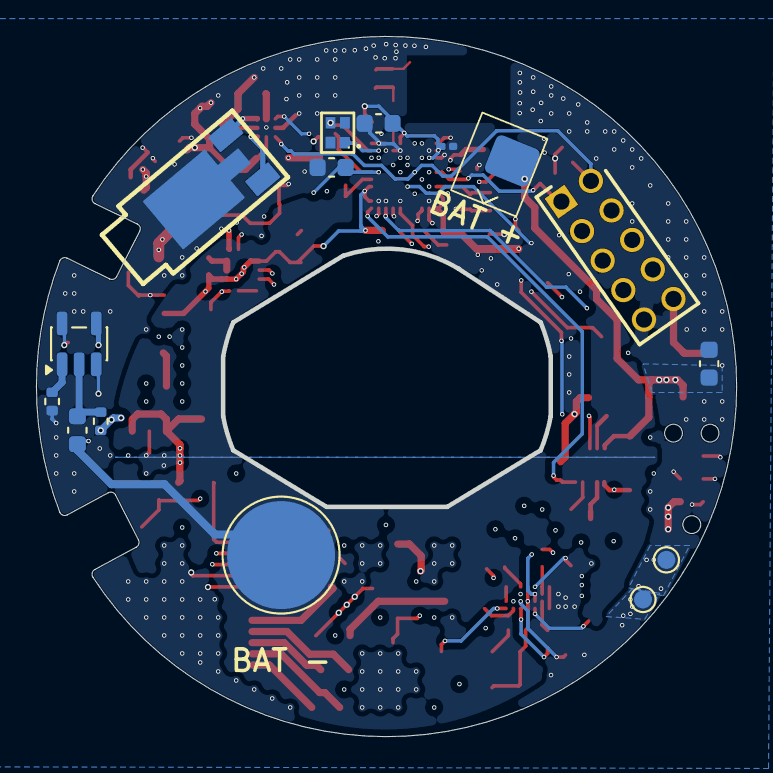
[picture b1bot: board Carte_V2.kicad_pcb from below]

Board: 6 copper layers, 38.9 x 38.9 mm, 113 parts (15 on the bottom side), 72 nets.

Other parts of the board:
R28: 4k7 Ohm; R_0402_1005Metric

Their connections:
/Capteurs/INTPA: R28.1; also elsewhere on the board

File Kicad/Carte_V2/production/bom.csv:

Designator,Footprint,Quantity,Value,LCSC Part #
AC1,LGA-14_1,1,LSM6DSOXTR,C481766
ANT1,ANT-SMD_4P-L3.2-W1.6,1,2450AT18D0100002E,C17410360
C0G2_50V1,0603,1,220nF,C21120
C0G3,0402,1,2n2F,C2987940
"C1, C14, C15, C16, C17, C2, C20, C30, C33, C34, C45, C51, C52",0603,13,1uF,C15849
"C10, C23, C9",0402,3,10nF,C15195
"C11, C4",0402,2,22nF,C1532
"C12, C13",0402,2,470nF,C92361
"C18, C21, C24, C27, C29, C31, C32, C37, C38, C40, C44, C48, C49, C53, C54, C55, C56",0402,17,100nF,C1525
C47,0201,1,100nF,C284966
"C19, C28, C35, C42, C43",0603,5,4u7F,C19666
"C25, C6, C7, C8",0603,4,10uF,C96446
C26,0402,1,100pF,C1546
"C36, C50",0402,2,12pF,C1547
C41,0603,1,2u2F,C23630
C46,0603,1,100nF,C14663
FL1,FILTER-SMD_6P-L1.6-W1.0-P0.50-BL,1,MLPF-WB55-02E3,C1855732
IC1,BGA28C40P4X7_188X301X50,1,BQ51003YFPT,C2650142
IC2,WSON-10_L2.0-W2.0-P0.40-BL-EP,1,BQ24040DSQR,C81080
IC4,SOT95P282X145-5N,1,TPS7A0218PDBVR,C3748843
IC6,SOT95P282X145-5N,1,TPS7A0233DBVR,C5142805
IC7,VEML6030,1,VEML6030,C132182
IC8,BGA9C50P3X3_144X144X62,1,DRV2605LYZFR,C2150692
L1,1008,1,10uH,C37428
M1,SMD_LD-SM-430-1,1,LD-SM-430,C41348533
Q1,TSOT-23,1,FDN338P,C2890130
Q2,TSOT-23,1,FDN335N,C845588
Q3,SOT-23-6_L2.9-W1.6-P0.95-LS2.8-BR,1,FS8205A,C2830320
R1,0402,1,4k53 Ohm,C3015988
"R11, R12, R18, R23, R27, R3, R4, R9",0402,8,10k Ohm,C25744
R13,0402,1,560k Ohm,C132339
"R14, R15",0402,2,47k Ohm,C25792
R16,0402,1,330 Ohm,C25104
"R17, R2",0402,2,2k Ohm,C4109
"R19, R20, R28",0402,3,4k7 Ohm,C25900
R22,0402,1,0 Ohm,C60485
"R25, R26",0402,2,1M Ohm,C26083
R5,0402,1,1.5k Ohm,C25867
R6,0402,1,187 Ohm,C39887
R8,0402,1,20k Ohm,C25765
"S1, S2",SKSLLAE010,2,SKSLLAE010,C139802
TH1,0402,1,10k NTC,C91636
U2,ST_WLCSP-100_4.4x4.38mm_Layout10x10_P0.4mm_Offcenter,1,STM32WB55VGYx,C1850399
U4,SOT-23-5,1,AP9101CAK-ATTRG1,C5588142
Y1,OSC-SMD_4P-L1.6-W1.2-BL,1,X1C032000B81H-HU,C254218
Y2,ECS32791210TR,1,ECS-.327-9-1210-TR,C2450044

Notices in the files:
Code/SmileWatch1/Core/Src/main.c:
Copyright (c) 2026 STMicroelectronics.
All rights reserved.
This software is licensed under terms that can be found in the LICENSE file
